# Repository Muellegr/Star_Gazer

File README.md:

****WIP****

PCB, Case, and Parts are currently ordered.  
Programming has not started.  

# Star_Gazer

An electrical engineering summer & fall project.  
A handheld device with a simple interface.  Point it at the sky and it will display information on constellations, stars, and planets

This is mainly an excuse to get back into electrical engineering after spending several months in a software engineering internship.  The focus of this was to gain more experiance with PCBs, digging into a microcontroller to flash & debug, and reinforce knowledge from my internship with programming.

The [ Bill Of Materials ](https://github.com/Muellegr/Star_Gazer/wiki)

The [ Schematic ](https://github.com/Muellegr/Star_Gazer/blob/master/Documentation/StarGazer_Schematics.pdf)

The [ PCB Layers ](https://github.com/Muellegr/Star_Gazer/blob/master/Documentation)

# DESIGN AND GOALS
## Push into scary unknowns
My classes have given me nice microcontroller boards with nicely formatted instructions with how to use and program with it.  Selecting a microcontroller, putting it on a PCB, and flashing it are all things I haven't had any experiance with.  It was a big scary unknown - jumping into it with this project lets me get experiance with it.
I also wanted to look at signal integrity but this was a smaller goal. I have several long awkward SPI/I2C traces which may allow for some learning.
### HARDWARE GOALS
* Place and program a microcontroller - I've only used nice premade boards, never my own.
* Unique shape and case - My previous project failed at the case design due to covid19.  I wanted to do something without the standard square PCB and case.
* Making an easier to assemble device. A preference was made to larger components, however some are small by necessity. 
### SOFTWARE GOALS
* C with databases - I wanted to deal with working with a database. The database will be kept simple and may end up becoming a packed array.  
* Testing - I want to create my own unit testing system for this for some parts. This is a low priority and meant to be more of a proof of concept.
* Microcontroller setup - Microcontrollers have manuals with hundreds of pages for using them.  This is intimidating.  

### Device
[ Phones have a ton of options for star gazing apps ](https://www.tomsguide.com/round-up/best-stargazing-apps)
These turn your phone into a sort of window into the night sky - hold it over a constellation, and the screen will show the constellation.  This project stems from those kinds of apps.
This isn't a replacement, nor is it a product.  This will cost more and be much less capable. But it will teach me a lot of things!

The shape of the device is ring like, where the inside of ring glows in the direction of constellations and important stars. As the device 'aims' at one of these object, the ring light will change shape and intensity to indicate distance and location.  When aimed at the object, a button can be pressed which will display information about this object (name, description..) on a small screen on the device.

[ Basic but more indepth description on finding orientation. ](https://github.com/Muellegr/Star_Gazer/wiki/Basic-idea-behind-orientation)

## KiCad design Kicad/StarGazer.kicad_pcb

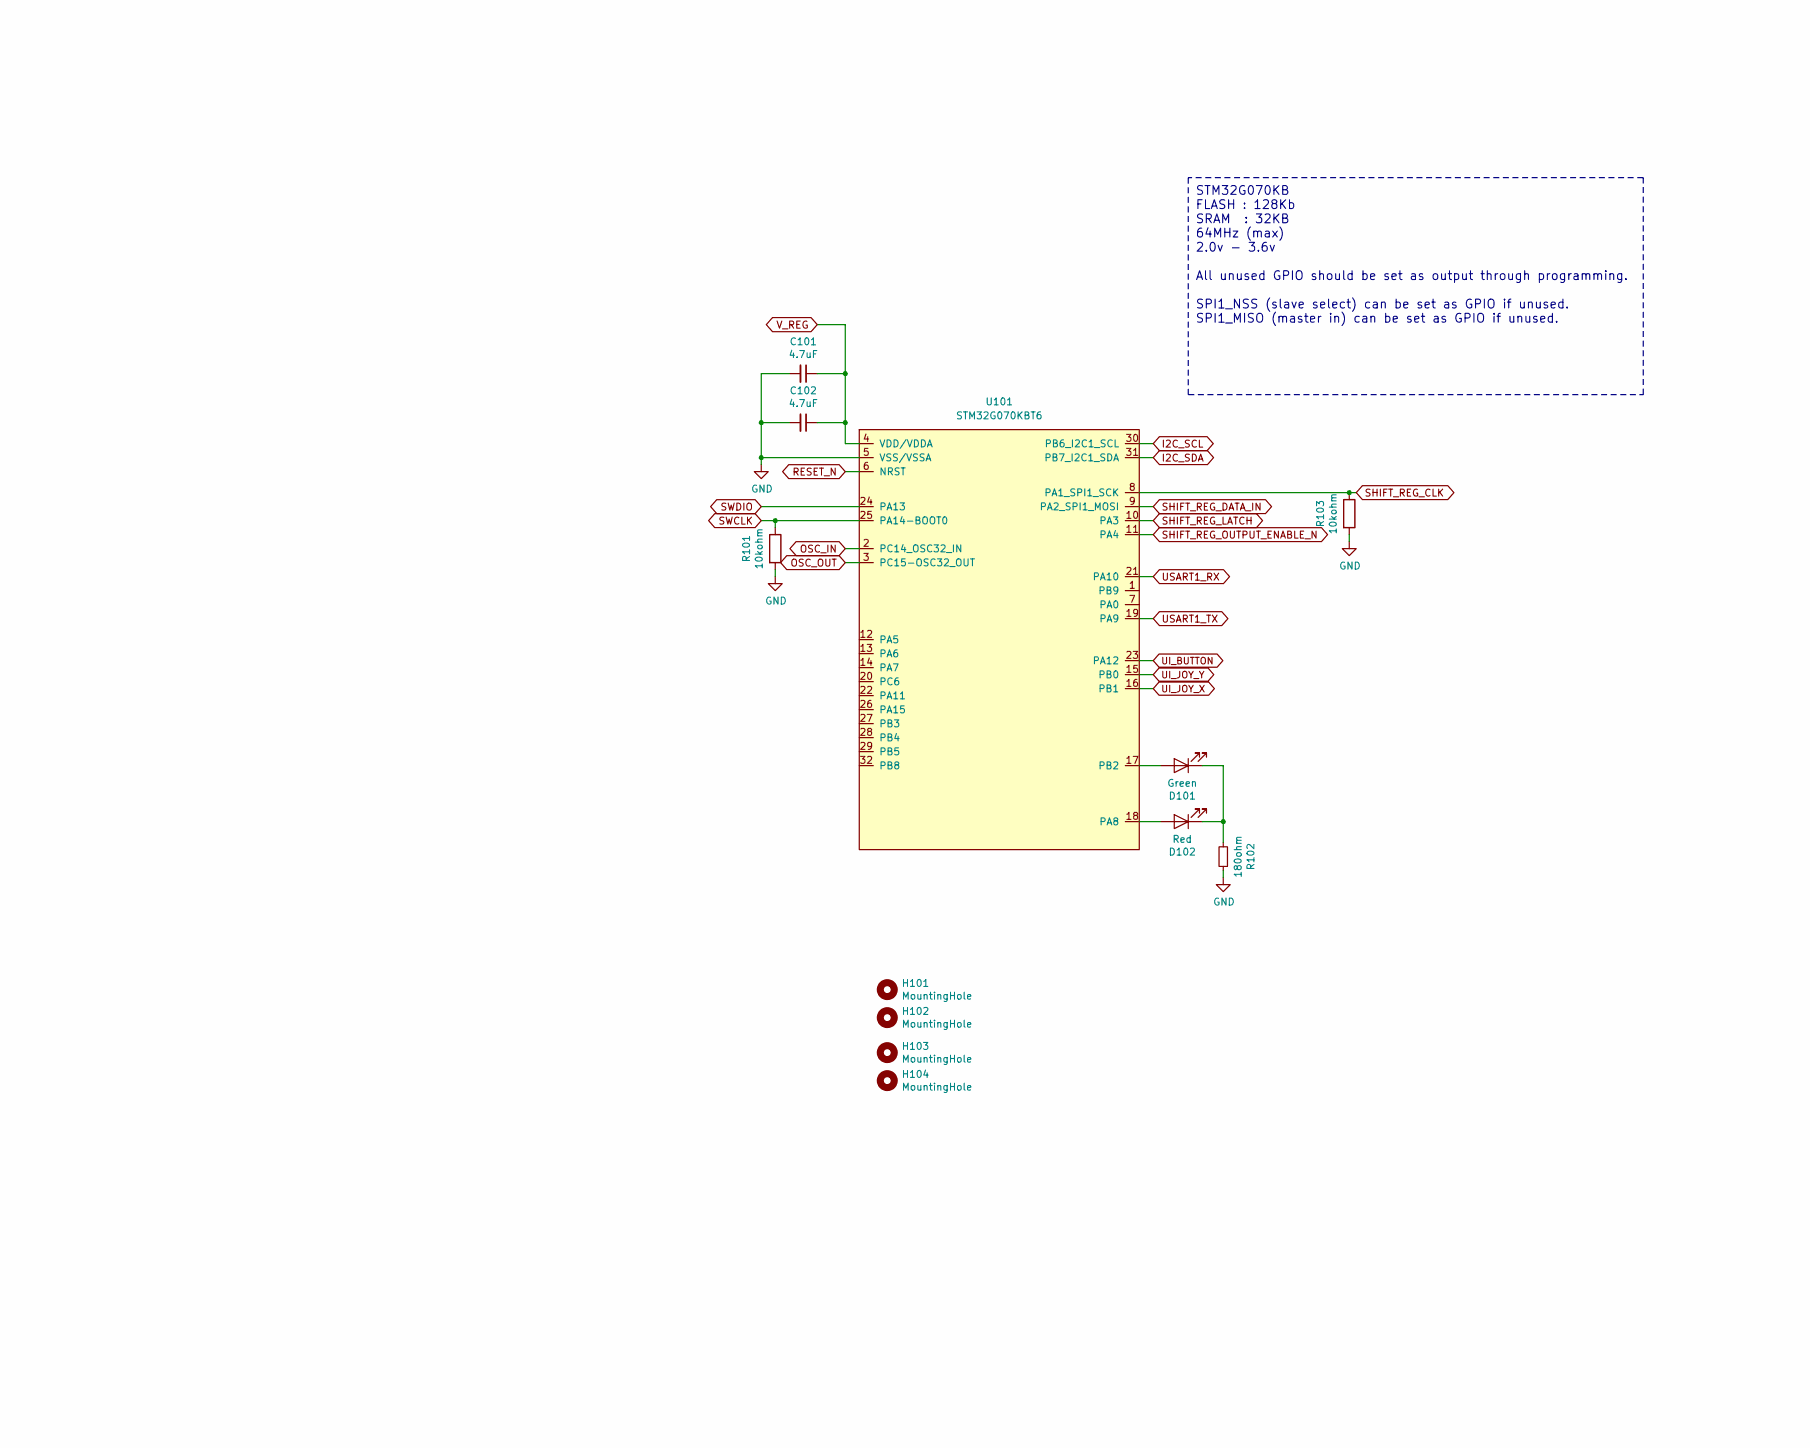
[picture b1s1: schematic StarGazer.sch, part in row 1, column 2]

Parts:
C101, C102: 4.7uF; C_0805_2012Metric_Pad1.15x1.40mm_HandSolder; part_name Capactitor - Bypass
D101: Green; D_1206_3216Metric; part_details Debug Light
D102: Red; D_1206_3216Metric; part_details Debug Light
H101, H102, H103, H104: MountingHole; MountingHole_3.2mm_M3; part_details DO_NOT_SHOW
R101, R103: 10kohm; R_1206_3216Metric_Pad1.42x1.75mm_HandSolder; part_name Resistor - Pull Up
R102: 180ohm; R_1206_3216Metric_Pad1.42x1.75mm_HandSolder; part_name Resistor - LED Status
U101: STM32G070KBT6; LQFP-32_7x7mm_P0.8mm; part_details 64Mhz Flash=128Kb, SRAM=32Kb

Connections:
GND: C101.2, C102.2, R101.2, R102.1, R103.2, U101.5 (VSS/VSSA); also elsewhere on the board
I2C_SCL: U101.30 (PB6_I2C1_SCL); also elsewhere on the board
I2C_SDA: U101.31 (PB7_I2C1_SDA); also elsewhere on the board
unnamed: D101.1 (K), D102.1 (K), R102.2
unnamed: D101.2 (A), U101.17 (PB2)
unnamed: D102.2 (A), U101.18 (PA8)
OSC_IN: U101.2 (PC14_OSC32_IN); also elsewhere on the board
OSC_OUT: U101.3 (PC15-OSC32_OUT); also elsewhere on the board
RESET_N: U101.6 (NRST); also elsewhere on the board
SHIFT_REG_CLK: R103.1, U101.8 (PA1_SPI1_SCK); also elsewhere on the board
SHIFT_REG_DATA_IN: U101.9 (PA2_SPI1_MOSI); also elsewhere on the board
SHIFT_REG_LATCH: U101.10 (PA3); also elsewhere on the board
SHIFT_REG_OUTPUT_ENABLE_N: U101.11 (PA4); also elsewhere on the board
SWCLK: R101.1, U101.25 (PA14-BOOT0); also elsewhere on the board
SWDIO: U101.24 (PA13); also elsewhere on the board
UI_BUTTON: U101.23 (PA12); also elsewhere on the board
UI_JOY_X: U101.16 (PB1); also elsewhere on the board
UI_JOY_Y: U101.15 (PB0); also elsewhere on the board
USART1_RX: U101.21 (PA10); also elsewhere on the board
USART1_TX: U101.19 (PA9); also elsewhere on the board
V_REG: C101.1, C102.1, U101.4 (VDD/VDDA); also elsewhere on the board

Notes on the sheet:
STM32G070KB FLASH : 128Kb SRAM : 32KB 64MHz (max) 2.0v - 3.6v All unused GPIO should be set as output through programming. SPI1_NSS (slave select) can be set as GPIO if unused. SPI1_MISO (master in) can be set as GPIO if unused.

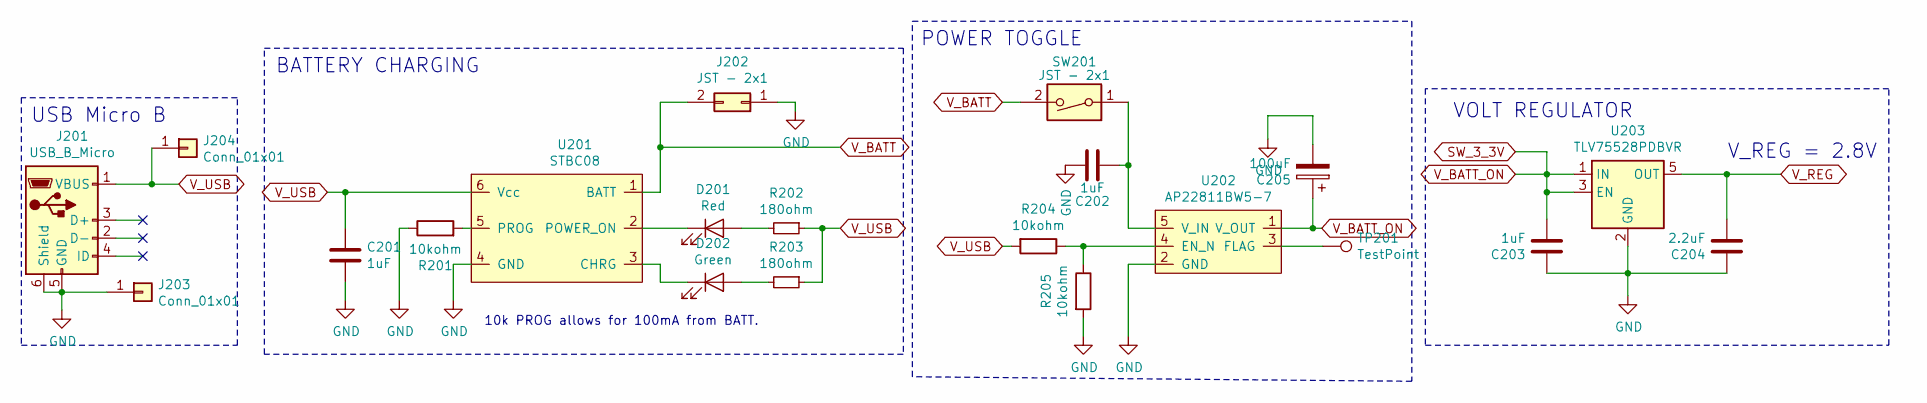
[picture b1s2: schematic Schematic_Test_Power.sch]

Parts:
C201, C202, C203: 1uF; C_0805_2012Metric_Pad1.15x1.40mm_HandSolder; part_name Capactitor - Bypass
C204: 2.2uF; C_0805_2012Metric_Pad1.15x1.40mm_HandSolder; part_name Capactitor - Bypass
C205: 100uF; CP_Elec_6.3x5.2; part_name Capactitor - Bypass
D201: Red; D_1206_3216Metric; part_details Red when charging error
D202: Green; D_1206_3216Metric; part_details Green when charging
J201: USB_B_Micro; USB_Micro-B_Amphenol_10103594-0001LF_Horizontal; part_name USB-B Micro
J202: JST - 2x1; JST_EH_B2B-EH-A_1x02_P2.50mm_Vertical; part_name Battery Connector
J203, J204: Conn_01x01; PinHeader_1x01_P2.00mm_Vertical; part_details DO_NOT_SHOW
R201: 10kohm; R_1206_3216Metric_Pad1.42x1.75mm_HandSolder; part_details Battery Program for 100mA recharge rate.
R202, R203: 180ohm; R_1206_3216Metric_Pad1.42x1.75mm_HandSolder; part_name Resistor - LED Status
R204, R205: 10kohm; R_1206_3216Metric_Pad1.42x1.75mm_HandSolder; part_name Resistor - Pull Up
SW201: JST - 2x1; JST_EH_B2B-EH-A_1x02_P2.50mm_Vertical; part_details Power toggle
TP201: TestPoint; TestPoint_Pad_D1.0mm; part_details Test point for U202 error (low imp. on 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
U201: STBC08; DFN-6-1EP_3x3mm_P0.95mm_EP1.7x2.6mm; part_name Lithium Ion Battery Charging IC
U202: AP22811BW5-7; TSOT-23-5_HandSoldering; part_details Battery protection switch
U203: TLV75528PDBVR; SOT-23-5; part_details 2.8v 500mA, 230mV~ dropout

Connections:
GND: C201.2, C202.2, C203.1, C204.1, C205.2, J201.5 (GND), J201.6 (Shield), J202.1, J203.1, R201.1, R205.2, U201.4 (GND), U202.2 (GND), U203.2 (GND); also elsewhere on the board
unnamed: C202.1, SW201.1, U202.5 (V_IN)
unnamed: D201.1 (K), U201.2 (POWER_ON)
unnamed: D201.2 (A), R202.2
unnamed: D202.1 (K), U201.3 (CHRG)
unnamed: D202.2 (A), R203.2
unnamed: R201.2, U201.5 (PROG)
unnamed: R204.1, R205.1, U202.4 (EN_N)
unnamed: TP201.1, U202.3 (FLAG)
SW_3_3V: C203.2, C205.1, U202.1 (V_OUT), U203.1 (IN), U203.3 (EN); also elsewhere on the board
V_BATT: J202.2, SW201.2, U201.1 (BATT)
V_REG: C204.2, U203.5 (OUT); also elsewhere on the board
V_USB: C201.1, J201.1 (VBUS), J204.1, R202.1, R203.1, R204.2, U201.6 (Vcc)

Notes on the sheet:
10k PROG allows for 100mA from BATT.
BATTERY CHARGING
POWER TOGGLE
VOLT REGULATOR
V_REG = 2.8V
USB Micro B

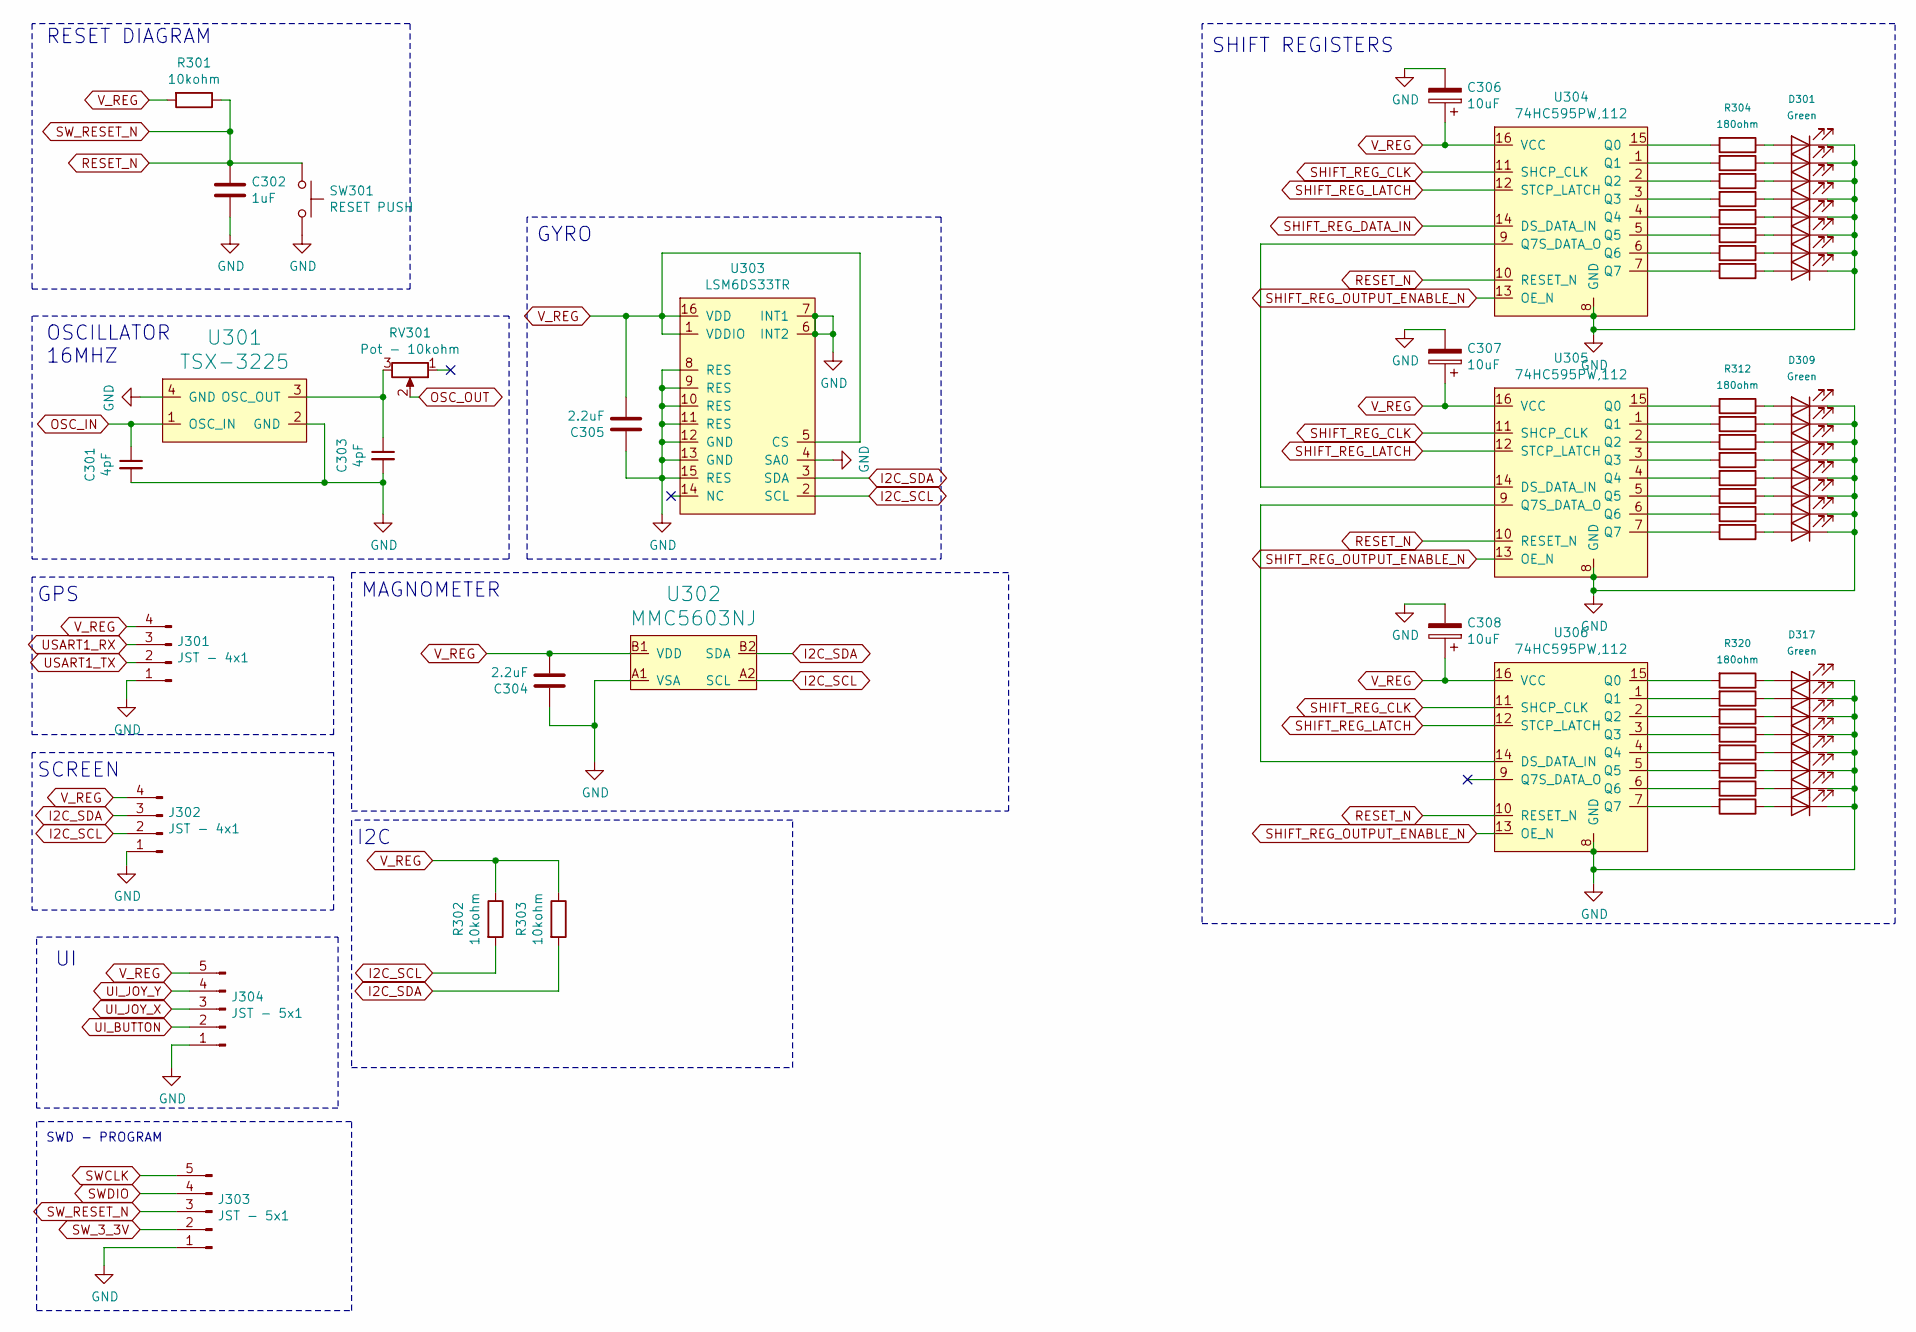
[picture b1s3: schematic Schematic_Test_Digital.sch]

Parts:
C301, C303: 4pF; C_0805_2012Metric_Pad1.15x1.40mm_HandSolder; part_name Capactitor - Crystal
C302: 1uF; C_0805_2012Metric_Pad1.15x1.40mm_HandSolder; part_name Capactitor - Bypass
C304, C305: 2.2uF; C_0805_2012Metric_Pad1.15x1.40mm_HandSolder; part_name Capactitor - Bypass
C306, C307, C308: 10uF; CP_Elec_4x3; part_name Capactitor - Bypass
D301, D302, D303, D304, D305, D306, D307, D308, D309, D310, D311, D312, D313, D314, D315, D316, D317, D318, D319, D320, D321, D322, D323, D324: Green; D_1206_3216Metric; part_name LED - Ring Green
J301: JST - 4x1; JST_EH_B4B-EH-A_1x04_P2.50mm_Vertical; part_details USART
J302: JST - 4x1; JST_EH_B4B-EH-A_1x04_P2.50mm_Vertical; part_details I2C
J303: JST - 5x1; JST_EH_B5B-EH-A_1x05_P2.50mm_Vertical; part_name SWD Program Connector
J304: JST - 5x1; JST_EH_B5B-EH-A_1x05_P2.50mm_Vertical; part_details I2C
R301, R302, R303: 10kohm; R_1206_3216Metric_Pad1.42x1.75mm_HandSolder; part_name Resistor - Pull Up
R304, R305, R306, R307, R308, R309, R310, R311, R312, R313, R314, R315, R316, R317, R318, R319, R320, R321, R322, R323, R324, R325, R326, R327: 180ohm; R_1206_3216Metric_Pad1.42x1.75mm_HandSolder; part_details LED dropout: 2v. V_REG is 2.8v. 0.8/180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
RV301: Pot - 10kohm; 35WR10KLFTR; part_details Adjustable external clock resistor.
SW301: RESET PUSH; SW_SPST_CK_RS282G05A3; part_name Switch - Reset (internal)
U301: TSX-3225; Crystal_SMD_SeikoEpson_TSX3225-4Pin_3.2x2.5mm_HandSoldering; part_name 16MHz Crystal
U302: MMC5603NJ; BGA_2_2; part_name Magnometer
U303: LSM6DS33TR; LGA-16_3x3mm_P0.5mm_LayoutBorder3x5y; part_name 6-axis Gyrometer
U304, U305, U306: 74HC595PW,112; TSSOP-16_4.4x5mm_P0.65mm; part_name Shift Register

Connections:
GND: C301.2, C302.2, C303.2, C304.1, C305.1, C306.2, C307.2, C308.2, D301.1 (K), D302.1 (K), D303.1 (K), D304.1 (K), D305.1 (K), D306.1 (K), D307.1 (K), D308.1 (K), D309.1 (K), D310.1 (K), D311.1 (K), D312.1 (K), D313.1 (K), D314.1 (K), D315.1 (K), D316.1 (K), D317.1 (K), D318.1 (K), D319.1 (K), D320.1 (K), D321.1 (K), D322.1 (K), D323.1 (K), D324.1 (K), J301.1, J302.1, J303.1, J304.1, SW301.2, U301.2 (GND), U301.4 (GND), U302.A1 (VSA), U303.4 (SA0), U303.6 (INT2), U303.7 (INT1), U303.8 (RES), U303.9 (RES), U303.10 (RES), U303.11 (RES), U303.12 (GND), U303.13 (GND), U303.15 (RES), U304.8 (GND), U305.8 (GND), U306.8 (GND); also elsewhere on the board
I2C_SCL: J302.2, R302.2, U302.A2 (SCL), U303.2 (SCL); also elsewhere on the board
I2C_SDA: J302.3, R303.2, U302.B2 (SDA), U303.3 (SDA); also elsewhere on the board
unnamed: C303.1, RV301.3, U301.3 (OSC_OUT)
unnamed: D301.2 (A), R304.1
unnamed: D302.2 (A), R305.1
unnamed: D303.2 (A), R306.1
unnamed: D304.2 (A), R307.1
unnamed: D305.2 (A), R308.1
unnamed: D306.2 (A), R309.1
unnamed: D307.2 (A), R310.1
unnamed: D308.2 (A), R311.1
unnamed: D309.2 (A), R312.1
unnamed: D310.2 (A), R313.1
unnamed: D311.2 (A), R314.1
unnamed: D312.2 (A), R315.1
unnamed: D313.2 (A), R316.1
unnamed: D314.2 (A), R317.1
unnamed: D315.2 (A), R318.1
unnamed: D316.2 (A), R319.1
unnamed: D317.2 (A), R320.1
unnamed: D318.2 (A), R321.1
unnamed: D319.2 (A), R322.1
unnamed: D320.2 (A), R323.1
unnamed: D321.2 (A), R324.1
unnamed: D322.2 (A), R325.1
unnamed: D323.2 (A), R326.1
unnamed: D324.2 (A), R327.1
unnamed: R304.2, U304.15 (Q0)
unnamed: R305.2, U304.1 (Q1)
unnamed: R306.2, U304.2 (Q2)
unnamed: R307.2, U304.3 (Q3)
unnamed: R308.2, U304.4 (Q4)
unnamed: R309.2, U304.5 (Q5)
unnamed: R310.2, U304.6 (Q6)
unnamed: R311.2, U304.7 (Q7)
unnamed: R312.2, U305.15 (Q0)
unnamed: R313.2, U305.1 (Q1)
unnamed: R314.2, U305.2 (Q2)
unnamed: R315.2, U305.3 (Q3)
unnamed: R316.2, U305.4 (Q4)
unnamed: R317.2, U305.5 (Q5)
unnamed: R318.2, U305.6 (Q6)
unnamed: R319.2, U305.7 (Q7)
unnamed: R320.2, U306.15 (Q0)
unnamed: R321.2, U306.1 (Q1)
unnamed: R322.2, U306.2 (Q2)
unnamed: R323.2, U306.3 (Q3)
unnamed: R324.2, U306.4 (Q4)
unnamed: R325.2, U306.5 (Q5)
unnamed: R326.2, U306.6 (Q6)
unnamed: R327.2, U306.7 (Q7)
unnamed: U304.9 (Q7S_DATA_O), U305.14 (DS_DATA_IN)
unnamed: U305.9 (Q7S_DATA_O), U306.14 (DS_DATA_IN)
OSC_IN: C301.1, U301.1 (OSC_IN); also elsewhere on the board
OSC_OUT: RV301.2; also elsewhere on the board
RESET_N: C302.1, J303.3, R301.1, SW301.1, U304.10 (RESET_N), U305.10 (RESET_N), U306.10 (RESET_N); also elsewhere on the board
SHIFT_REG_CLK: U304.11 (SHCP_CLK), U305.11 (SHCP_CLK), U306.11 (SHCP_CLK); also elsewhere on the board
SHIFT_REG_DATA_IN: U304.14 (DS_DATA_IN); also elsewhere on the board
SHIFT_REG_LATCH: U304.12 (STCP_LATCH), U305.12 (STCP_LATCH), U306.12 (STCP_LATCH); also elsewhere on the board
SHIFT_REG_OUTPUT_ENABLE_N: U304.13 (OE_N), U305.13 (OE_N), U306.13 (OE_N); also elsewhere on the board
SWCLK: J303.5; also elsewhere on the board
SWDIO: J303.4; also elsewhere on the board
SW_3_3V: J303.2; also elsewhere on the board
UI_BUTTON: J304.2; also elsewhere on the board
UI_JOY_X: J304.3; also elsewhere on the board
UI_JOY_Y: J304.4; also elsewhere on the board
USART1_RX: J301.3; also elsewhere on the board
USART1_TX: J301.2; also elsewhere on the board
V_REG: C304.2, C305.2, C306.1, C307.1, C308.1, J301.4, J302.4, J304.5, R301.2, R302.1, R303.1, U302.B1 (VDD), U303.1 (VDDIO), U303.5 (CS), U303.16 (VDD), U304.16 (VCC), U305.16 (VCC), U306.16 (VCC); also elsewhere on the board

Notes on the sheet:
OSCILLATOR 16MHZ
SHIFT REGISTERS
SCREEN
I2C
GYRO
RESET DIAGRAM
SWD - PROGRAM
GPS
MAGNOMETER

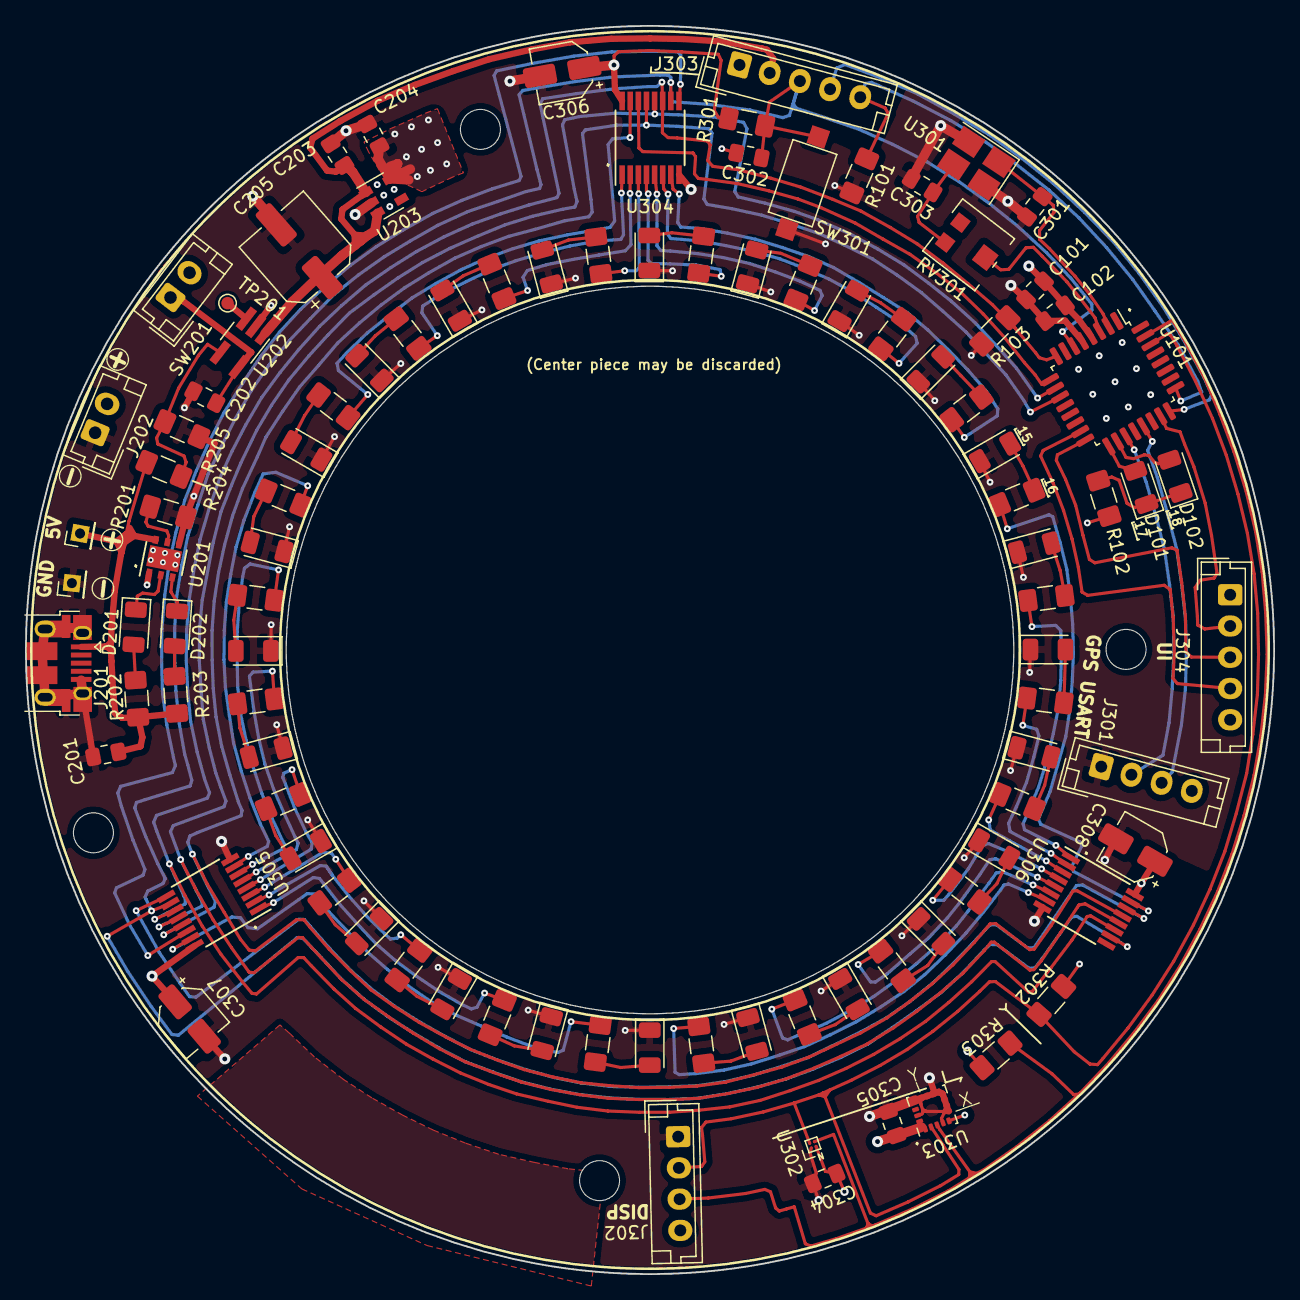
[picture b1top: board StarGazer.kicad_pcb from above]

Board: 4 copper layers, 99.9 x 99.9 mm, 104 parts (0 on the bottom side), 83 nets.

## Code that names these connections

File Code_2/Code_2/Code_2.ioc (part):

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Mcu.Name=STM32G070KBTx
Mcu.Package=LQFP32
Mcu.UserName=STM32G070KBTx
PA1.GPIOParameters=GPIO_Label
PA1.GPIO_Label=SPI_CLK_SHIFT_REG
PA1.Mode=TX_Only_Simplex_Unidirect_Master
PA1.Signal=SPI1_SCK
PA10.Mode=Synchronous
PA10.Signal=USART1_RX
PA12\ [PA10].GPIOParameters=GPIO_Label
PA12\ [PA10].GPIO_Label=UI_BUTTON
PA12\ [PA10].Signal=GPIO_Input
PA13.Mode=Serial_Wire
PA13.Signal=SYS_SWDIO
PA14-BOOT0.Mode=Serial_Wire
PA14-BOOT0.Signal=SYS_SWCLK
PA2.GPIOParameters=GPIO_Label
PA2.GPIO_Label=SPI_MOSI_SHIFT_REG_DATA
PA2.Mode=TX_Only_Simplex_Unidirect_Master
PA2.Signal=SPI1_MOSI
PA3.GPIOParameters=GPIO_Label
PA3.GPIO_Label=SHIFT_REG_LATCH
PA3.Signal=GPIO_Output
PA4.GPIOParameters=GPIO_Label
PA4.GPIO_Label=SHIFT_REG_OUTPUT_ENABLE_N
PA4.Signal=GPIO_Output
PA8.GPIOParameters=GPIO_Label
PA8.GPIO_Label=LED_RED
PA8.Signal=GPIO_Output
PA9.Mode=Synchronous
PA9.Signal=USART1_TX
PB0.GPIOParameters=GPIO_Label
PB0.GPIO_Label=UI_JOY_Y
PB0.Signal=GPIO_Analog
PB1.GPIOParameters=GPIO_Label
PB1.GPIO_Label=UI_JOY_X
PB1.Signal=GPIO_Analog
PB2.GPIOParameters=GPIO_Label
PB2.GPIO_Label=LED_GREEN
PB2.Signal=GPIO_Output
PB3.Mode=Synchronous
PB3.Signal=USART1_CK
PB6.Mode=I2C
PB6.Signal=I2C1_SCL
PB7.Mode=I2C
PB7.Signal=I2C1_SDA
PC14-OSC32_IN\ (PC14).Mode=LSE-External-Oscillator
PC14-OSC32_IN\ (PC14).Signal=RCC_OSC32_IN
PC15-OSC32_OUT\ (PC15).Mode=LSE-External-Oscillator
PC15-OSC32_OUT\ (PC15).Signal=RCC_OSC32_OUT
RCC.HSE_VALUE=8000000
RCC.SYSCLKFreq_VALUE=16000000
board=custom

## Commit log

2020-07-14 Added document folder. No real work has been prepared.
2020-08-22 Initial repo created, added some documents.
2020-08-22 Added current Kicad project.
2020-08-23 Continued devolopment -Added battery charging circuit -Added power toggle to prevent over charging battery -Added voltage regulator
2020-08-28 Added screen, gyro, and magnometer. Updated schematic parts.
2020-08-30 Changed linear voltage regulator from 1.7v to 2.8v This is done as I will be removing voltage regulators from some external parts (GPS, screen) and wiring in V_REG directly to them. These usually tak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
2020-09-01 Added oscillator.
    Primary part selection is complete.
2020-09-03 Assigning foot prints and testing GitHub as a site to document project with images.
2020-09-03 Testing smaller PNG
2020-09-03 BMP image test
2020-09-03 Moved major schematic parts to their own sheets - unknown if they have brought about issues because of this. Updated reference IDs.
2020-09-04 Corrected some schematic labeling.
2020-09-07 Assigned footprints to majority of refs. Missing is i2c due to unknown trace length.
2020-09-08 Continued (slow) devolopment.
    PCB board has begun. Parts are pushed out to where they need to roughly be.
2020-09-08 "PREVIOUS COMMIT MAIN SCHEMATIC CORRUPTED (???). Used commit before that."
2020-09-08 End of night, progress continues.
    Parts are getting initial placement.
    confidence raises.
2020-09-09 Switching magnometer with an updated part. This change is due to the limitations of JLCPCB's ball grid array. The ball diameter is 0.25mm, while the component has 0.2 While this could probably be wor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
    It is twice the cost of the orignal part and requires more support components, but is otherwhys an upgrade.
2020-09-09 Updated magnometer to LIS3MDL which has a more sane footprint.
2020-09-09 Discovered small bug with BoM script. It does not acccount for all parameters, such as foot print. This resulted in it thinking a electro-cap could be a ceramic-cap since they shared the same value.
    To simplify parts, C310 is now a ceramic cap at the same value.
2020-09-10 Preparing to begin placing parts on actual PCB
2020-09-11 Center LED ring laid out and connected. Other components will begin to be fitted into place. Silk screen has not been touched.
2020-09-13 Many parts are now placed on PCB.
    Work left off on MC, gyro, and mag.
    Discovered free-angle mode for traces, which will make connections look better in the future.
2020-09-14 All parts on board and routed. Beginning final part compatibility check. Big TODO is select GPS, verify parts, and begin route-polish step.
2020-09-15 Calculating ram needed and current selected chip will not fit it. Upgrading to a more capable chip.
2020-09-16 Upgraded to STM32G0 for increased memory. Schematic and PCB are updated. PCB now has radial grid applied in preparation of final part placement.
2020-09-16 Shift register tracing remade to curved. Hand hurty
2020-09-17 PCB updated to curved traces. Leftover final polish, screw locations, drill-routing, and art is missing
2020-09-18 Added screw locations.
2020-09-21 Continued work on PCB. Added back art.
2020-09-23 Working on case. Base cutouts took time but should now be complete. Height from top to bottom of 50mm.
2020-09-25 PCB is likely complete. Added USART for GPS. Added background art and front label. Some leftover things are needed for the case.
2020-09-28 Purchases made, case ordered, PCB ordered, parts ordered, money not happy.
2020-09-30 Added images
2020-09-30 Updated files
2020-09-30 Added proper file locations for schematic and pcb views
2020-10-07 Added case pictures
2020-10-07 image resize
2020-10-15 Added images. Small schematic corrections
2020-10-18 Added pictures
2020-11-06 Added code repo. Intention is to remove Hal drivers and write my own at some point. For now, let's have the code backed up while I work on it...
2020-11-09 Debugging on magnometer, believe the device is broken due to readings. Screen is set to debug
